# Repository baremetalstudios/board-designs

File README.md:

board-designs
=============

Bare Metal Studios designs. All designs are under Creative Commons licence.

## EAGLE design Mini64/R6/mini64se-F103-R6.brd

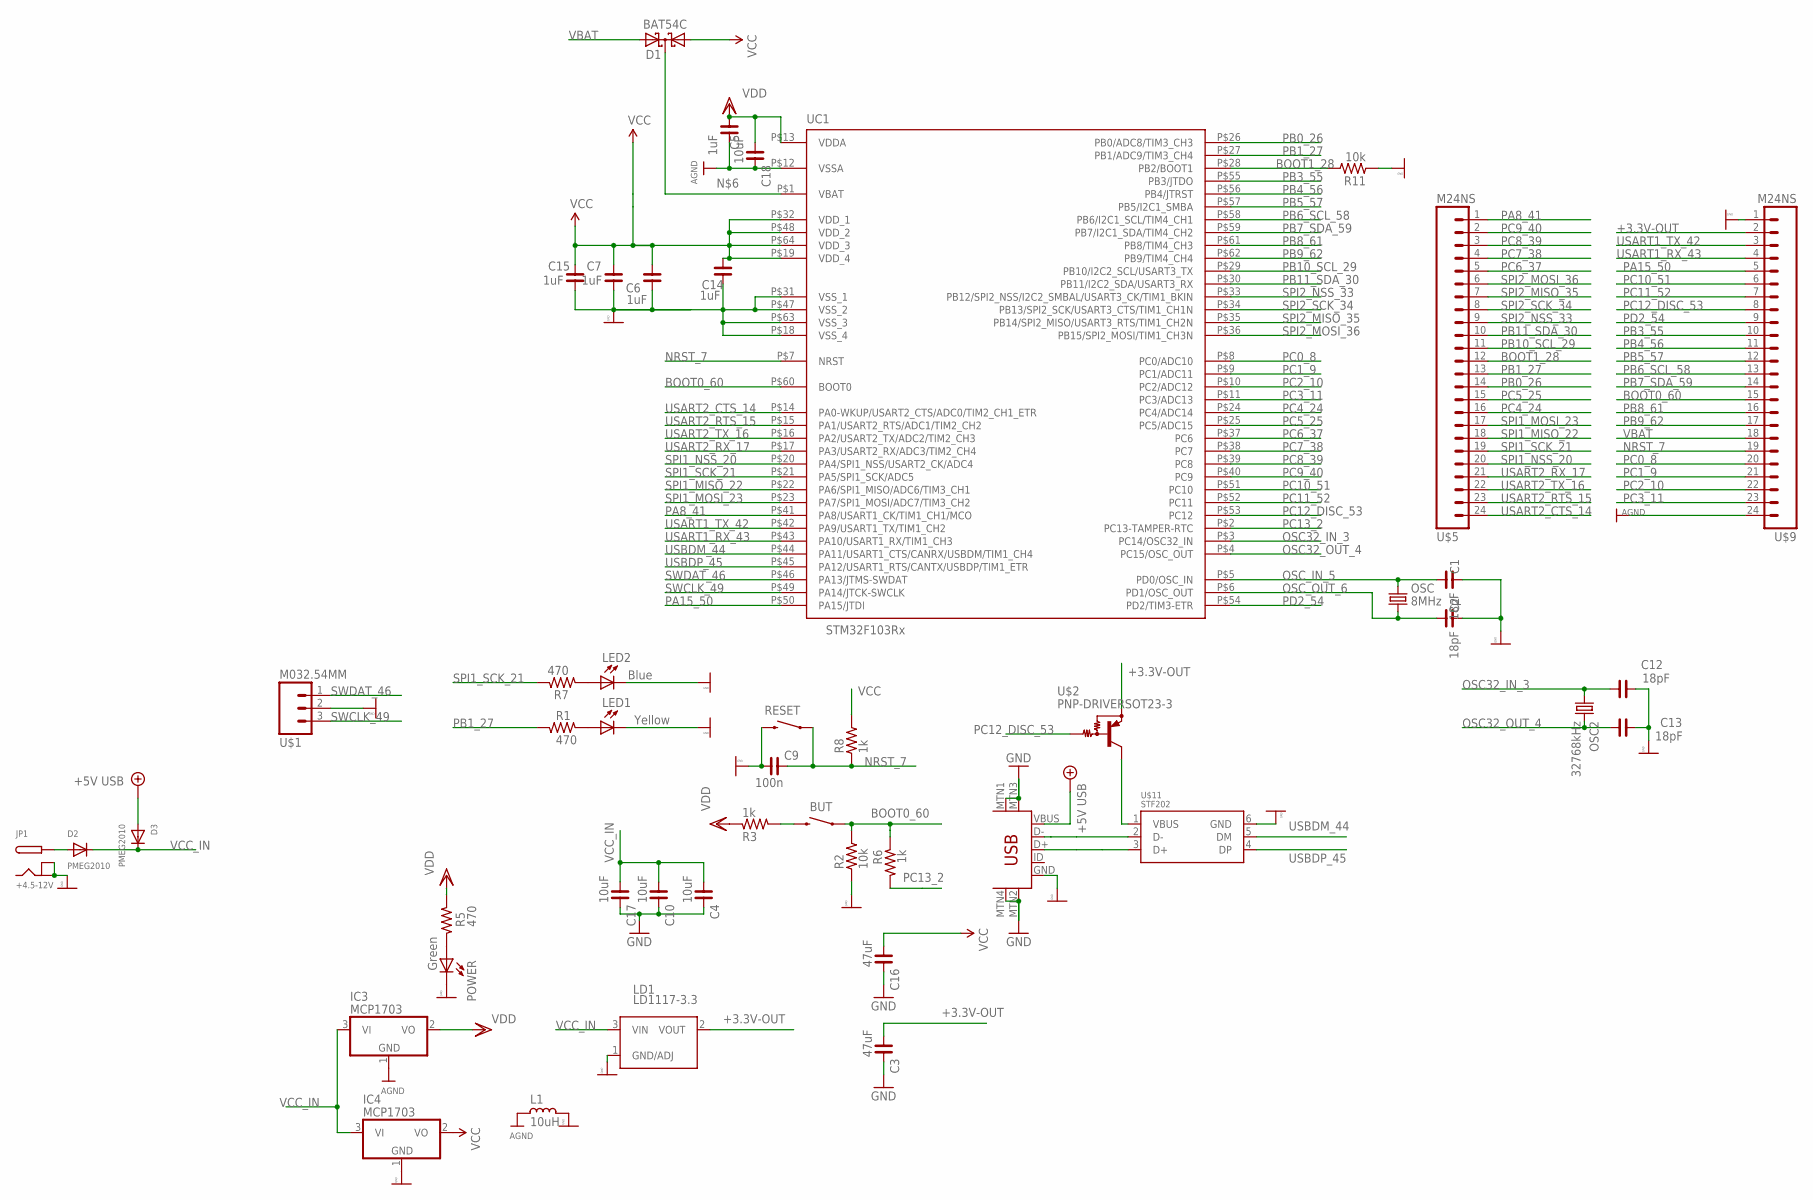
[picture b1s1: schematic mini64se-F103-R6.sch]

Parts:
BUT: SWITCH-MOMENTARY-2-N59; TACTILE-SWITCH-N59
C1, C2, C12, C13: 18pF; C0603
C3, C16: 47uF; C0805
C4, C10, C17, C18: 10uF; C0603
C5, C6, C7, C14, C15: 1uF; C0603
C9: 100n; C0603
D1: BAT54C; SOT23-3
D2, D3: PMEG2010; SOD-323
IC3, IC4: MCP1703; SOT23-3
JP1: +4.5-12V; DC-020-001
L1: 10uH; L0603
LD1: LD1117-3.3; SOT223
LED1: Yellow; CHIP-LED0603
LED2: Blue; CHIP-LED0603
OSC: 8MHz; HC49U-V
OSC2: 32768kHz; TC26H-M
POWER: Green; CHIP-LED0603
R1, R5, R7: 470; R0603
R2, R11: 10k; R0603
R3, R6, R8: 1k; R0603
RESET: SWITCH-MOMENTARY-2-N59; TACTILE-SWITCH-N59
U$1: M032.54MM; 1X03_NO_SILK
U$2: PNP-DRIVERSOT23-3; SOT23-3
U$5, U$9: M24NS; 1X24_NO_SILK
U$11: STF202; TSOP-6
UC1: STM32F103Rx; TQFP-10X10-64
USB: USB-MINIB-5PIN; USB-MINIB

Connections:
+3.3V-OUT: C3.1, LD1.2 (VOUT), U$2.2 (E), U$9.2 (3)
+5V: D3.A, USB.VBUS
AGND: C5.1, C18.2, IC3.1 (GND), L1.2, U$9.24 (25), UC1.P$12 (VSSA)
BOOT0_60: BUT.P$1 (1), R2.2, R6.1, U$9.15 (16), UC1.P$60 (BOOT0)
BOOT1_28: R11.2, U$5.12 (13), UC1.P$28 (PB2/BOOT1)
EXT_PWR: D2.A, JP1.PWR
GND: C1.1, C2.1, C3.2, C4.2, C6.1, C7.1, C9.1, C10.2, C12.1, C13.1, C14.1, C15.1, C16.2, C17.2, IC4.1 (GND), JP1.GND, JP1.GNDBREAK, L1.1, LD1.1 (GND/ADJ), LED1.C, LED2.C, POWER.C, R2.1, R11.1, RESET.P$2 (2), U$1.2, U$9.1 (2), U$11.6 (GND), UC1.P$18 (VSS_4), UC1.P$31 (VSS_1), UC1.P$47 (VSS_2), UC1.P$63 (VSS_3), USB.GND, USB.MTN1 (MTN2), USB.MTN2 (MTN3), USB.MTN3 (MTN1), USB.MTN4
unnamed: POWER.A, R5.2
unnamed: BUT.P$2 (2), R3.2
unnamed: LED2.A, R7.2
unnamed: LED1.A, R1.1
unnamed: D1.3 (CC), UC1.P$1 (VBAT)
unnamed: U$2.3 (C), U$11.1 (VBUS)
unnamed: U$11.2 (D-), USB.D-
unnamed: U$11.3 (D+), USB.D+
NRST_7: C9.2, R8.1, RESET.P$1 (1), U$9.19 (20), UC1.P$7 (NRST)
OSC32_IN_3: C12.2, OSC2.1, UC1.P$3 (PC14/OSC32_IN)
OSC32_OUT_4: C13.2, OSC2.2, UC1.P$4 (PC15/OSC_OUT)
OSC_IN_5: C1.2, OSC.2, UC1.P$5 (PD0/OSC_IN)
OSC_OUT_6: C2.2, OSC.1, UC1.P$6 (PD1/OSC_OUT)
PA8_41: U$5.1 (2), UC1.P$41 (PA8/USART1_CK/TIM1_CH1/MCO)
PA15_50: U$9.5 (6), UC1.P$50 (PA15/JTDI)
PB0_26: U$5.14 (15), UC1.P$26 (PB0/ADC8/TIM3_CH3)
PB1_27: R1.2, U$5.13 (14), UC1.P$27 (PB1/ADC9/TIM3_CH4)
PB3_55: U$9.10 (11), UC1.P$55 (PB3/JTDO)
PB4_56: U$9.11 (12), UC1.P$56 (PB4/JTRST)
PB5_57: U$9.12 (13), UC1.P$57 (PB5/I2C1_SMBA)
PB6_SCL_58: U$9.13 (14), UC1.P$58 (PB6/I2C1_SCL/TIM4_CH1)
PB7_SDA_59: U$9.14 (15), UC1.P$59 (PB7/I2C1_SDA/TIM4_CH2)
PB8_61: U$9.16 (17), UC1.P$61 (PB8/TIM4_CH3)
PB9_62: U$9.17 (18), UC1.P$62 (PB9/TIM4_CH4)
PB10_SCL_29: U$5.11 (12), UC1.P$29 (PB10/I2C2_SCL/USART3_TX)
PB11_SDA_30: U$5.10 (11), UC1.P$30 (PB11/I2C2_SDA/USART3_RX)
PC0_8: U$9.20 (21), UC1.P$8 (PC0/ADC10)
PC1_9: U$9.21 (22), UC1.P$9 (PC1/ADC11)
PC2_10: U$9.22 (23), UC1.P$10 (PC2/ADC12)
PC3_11: U$9.23 (24), UC1.P$11 (PC3/ADC13)
PC4_24: U$5.16 (17), UC1.P$24 (PC4/ADC14)
PC5_25: U$5.15 (16), UC1.P$25 (PC5/ADC15)
PC6_37: U$5.5 (6), UC1.P$37 (PC6)
PC7_38: U$5.4 (5), UC1.P$38 (PC7)
PC8_39: U$5.3 (4), UC1.P$39 (PC8)
PC9_40: U$5.2 (3), UC1.P$40 (PC9)
PC10_51: U$9.6 (7), UC1.P$51 (PC10)
PC11_52: U$9.7 (8), UC1.P$52 (PC11)
PC12_DISC_53: U$2.1 (B), U$9.8 (9), UC1.P$53 (PC12)
PC13_2: R6.2, UC1.P$2 (PC13-TAMPER-RTC)
PD2_54: U$9.9 (10), UC1.P$54 (PD2/TIM3-ETR)
SPI1_MISO_22: U$5.18 (19), UC1.P$22 (PA6/SPI1_MISO/ADC6/TIM3_CH1)
SPI1_MOSI_23: U$5.17 (18), UC1.P$23 (PA7/SPI1_MOSI/ADC7/TIM3_CH2)
SPI1_NSS_20: U$5.20 (21), UC1.P$20 (PA4/SPI1_NSS/USART2_CK/ADC4)
SPI1_SCK_21: R7.1, U$5.19 (20), UC1.P$21 (PA5/SPI1_SCK/ADC5)
SPI2_MISO_35: U$5.7 (8), UC1.P$35 (PB14/SPI2_MISO/USART3_RTS/TIM1_CH2N)
SPI2_MOSI_36: U$5.6 (7), UC1.P$36 (PB15/SPI2_MOSI/TIM1_CH3N)
SPI2_NSS_33: U$5.9 (10), UC1.P$33 (PB12/SPI2_NSS/I2C2_SMBAL/USART3_CK/TIM1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)
SPI2_SCK_34: U$5.8 (9), UC1.P$34 (PB13/SPI2_SCK/USART3_CTS/TIM1_CH1N)
SWCLK_49: U$1.3, UC1.P$49 (PA14/JTCK-SWCLK)
SWDAT_46: U$1.1, UC1.P$46 (PA13/JTMS-SWDAT)
USART1_RX_43: U$9.4 (5), UC1.P$43 (PA10/USART1_RX/TIM1_CH3)
USART1_TX_42: U$9.3 (4), UC1.P$42 (PA9/USART1_TX/TIM1_CH2)
USART2_CTS_14: U$5.24 (25), UC1.P$14 (PA0-WKUP/USART2_CTS/ADC0/TIM2_CH1_ETR)
USART2_RTS_15: U$5.23 (24), UC1.P$15 (PA1/USART2_RTS/ADC1/TIM2_CH2)
USART2_RX_17: U$5.21 (22), UC1.P$17 (PA3/USART2_RX/ADC3/TIM2_CH4)
USART2_TX_16: U$5.22 (23), UC1.P$16 (PA2/USART2_TX/ADC2/TIM2_CH3)
USBDM_44: U$11.5 (DM), UC1.P$44 (PA11/USART1_CTS/CANRX/USBDM/TIM1_CH4)
USBDP_45: U$11.4 (DP), UC1.P$45 (PA12/USART1_RTS/CANTX/USBDP/TIM1_ETR)
VBAT: D1.2 (A2), U$9.18 (19)
VCC: C6.2, C7.2, C14.2, C15.2, C16.1, D1.1 (A1), IC4.2 (VO), R8.2, UC1.P$19 (VDD_4), UC1.P$32 (VDD_1), UC1.P$48 (VDD_2), UC1.P$64 (VDD_3)
VCC_IN: C4.1, C10.1, C17.1, D2.C, D3.C, IC3.3 (VI), IC4.3 (VI), LD1.3 (VIN)
VDD: C5.2, C18.1, IC3.2 (VO), R3.1, R5.1, UC1.P$13 (VDDA)

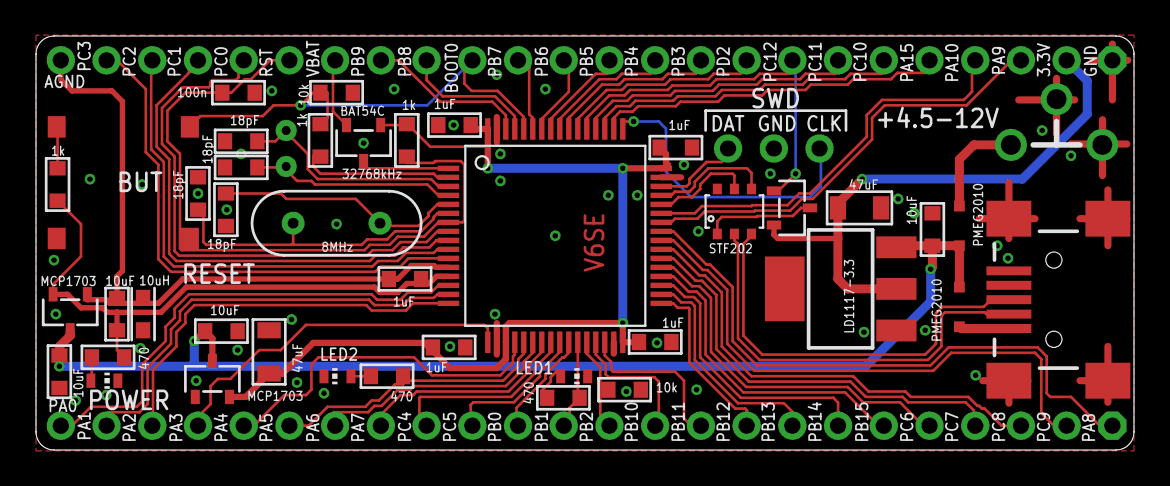
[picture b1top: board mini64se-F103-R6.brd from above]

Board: 2 copper layers, 61.0 x 23.0 mm, 46 parts (0 on the bottom side), 70 nets.

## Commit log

2013-12-30 Added Mini64 R6 design files.
